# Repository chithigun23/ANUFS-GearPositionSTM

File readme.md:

# GearSensor STM32

Gear position sensor board for a MoTeC M150 paddle-shift system: an `STM32F072` reads a linear position sensor and the neutral switch, works out the current gear, and reports it to the ECU as an analog voltage, with a CAN transceiver on the ECU bus and status LEDs on the board. Powered from the M150 sensor 5 V or USB-C, and replaces the Arduino UNO R4 WiFi and shield build described on the [GearSensor project page](https://chithigunatilake.com/GearSensor/).

## Architecture

- **Power** - 5 V in from the M150 sensor supply (`SEN_5V`, J3) or from USB-C VBUS (`J1`). A `TPS2116` power mux (`U2`) gives the car priority and falls back to USB when the car rail drops below about 4 V (set by `R3`/`R4`, 300 k / 100 k). It blocks reverse current, so the ECU supply is never back-fed from a laptop and the laptop is never back-fed from the car. The mux status pin goes to `PA2` (`MUX_STAT`: high = car, low = USB). 1 uF on each mux input, a 300 mA polyfuse (`F1`) on the mux output and an `AP2112K-3.3` LDO (`U1`) after it. There is no reverse-polarity stage because a sensor supply cannot be reversed by the battery.
- **Compute** - `STM32F072CB` (`U6`, LQFP-48) with a 24 MHz `ABM8AIG` crystal on HSE, which CAN needs for accurate bit timing. Ferrite-filtered VDDA (`FB1`, with `C18` 1 uF and `C19` 10 nF after it), NRST and BOOT0 buttons.
- **Position and neutral sensing** - linear position sensor on J3 pin 7, scaled by `R5`/`R6` (10 k / 15 k) so a 5 V sensor swing lands inside the 3.3 V ADC range on `PA0`, with a 100 nF filter (`C20`) at the pin. Neutral switch on J3 pin 6 into `PB2` through `R28` (1 k). An `AQ1005-01ETG` TVS (`D1`, `D2`) on each harness input.
- **Gear output** - the STM32's own 12-bit DAC on `PA4` (output buffer off, so it can reach 0 V) drives a `TLV9062` op-amp (`U4`) at a gain of 1.5 (`R11` 4.99 k / `R12` 10 k) from the 5 V rail, giving the gear-position voltage on J3 pin 3 up to about 4.1 V through two 390 ohm 0603 series resistors (`R29`/`R30`) and a TVS (`D3`). `R10` (1 M) holds the output at 0 V until the firmware enables the DAC. A 10 k / 15 k divider (`R14`/`R15`, filtered by `C21`) reads the output back on `PA1` for closed-loop trim. The unused op-amp channel is tied off as a follower.
- **Status LEDs** - six `XL-2012SURUGC` red/green LEDs: `LED1` to `LED4` show the gear (or a fault) in combination, `LED5` shows MCU status and `LED6` shows the neutral switch. Their anodes share an `LED_5V` rail behind the slide switch `SW3`, which turns every LED off. Each die has its own series resistor (390 ohm red, 680 ohm green) and is sunk by a 5 V-tolerant MCU pin, so no driver is needed.
- **CAN** - `TCAN337` 3.3 V transceiver (`U5`) on `PB9` / `PB8`, with fault on `PB0` and silent mode on `PB1`. CAN+ / CAN- on J3 pins 5 and 4.
- **Debug and USB** - `J1` USB-C with 5.1 k CC pull-downs and a `USBLC6-2SC6` ESD array (`U3`) on D+ / D- into the MCU's native USB (`PA11` / `PA12`). 4-pin SWD header `J2` and a Tag-Connect TC2030 footprint `J4` (pads only, nothing to buy) on the same SWD, reset and 3.3 V nets. Test pads on the rails and every external signal.

The diagram is animated: dashes show the direction of flow, amber for power, teal for signals, blue for buses. If your viewer does not animate SVGs, the arrows still show the same paths.

## Car connector (J3)

Solder-wire pigtails, not a board connector: eight PTH pads in a row along the bottom edge (`gear:SolderWire-0.5sqmm_1x08_P4.2mm_D0.9mm_OD2.1mm_Relief_Anchored`, 1.15 mm holes for 0.5 mm² or smaller wire, 4.2 mm pitch), pin 1 on the right, labelled on both sides.

The pads are built not to tear out:

- **Annular ring:** 3.0 mm pads on 1.15 mm holes (0.93 mm ring), on all four copper layers, so the inner layers also hold the barrel.
- **Anchor vias:** two plated 0.3 mm vias inside each pad, on the side away from the relief hole (opposite the pull), through every layer. They rivet the pad copper to the board, and the GND pin's vias will also tie into the ground planes when they are poured.
- **Strain relief:** a 2.3 mm hole 3.6 mm from each pad towards the board edge, for insulation up to about 2.1 mm. The hole is plated (no net) so the wire bears on a smooth copper barrel instead of cut glass fibre, which chafes insulation under vibration. A silk ring marks each one, and "STRAIN RELIEF HOLES - DO NOT SOLDER" is printed directly under the row on both sides.

Fitting a wire: bring it in from the edge on the underside, up through its relief hole, across the top, and down into its pad, then solder it on the underside. Do not solder the relief hole. A pull on the harness then loads the relief hole, not the solder joint.

- **Vibration:** use abrasion-resistant insulation (ETFE/Tefzel, as most car harnesses do) and stake each wire to the board with RTV or a flexible adhesive at the relief hole and the pad. That stops the wire moving, which is what chafes the insulation and fatigues the wire where the solder stops wicking.
- **Edge web:** the board is 2 mm taller than square (50 x 52 mm) so there is 2.8 mm of FR4 between each relief hole and the bottom edge, which takes the pull. Still clamp the harness at the enclosure gland, so its weight does not hang off the board.

There are no cable-tie slots: the only free board edge beside the pigtail row is taken by the M3 mounting holes and their standoffs, so tie the harness to the enclosure at the cable gland instead.

| Pin | Net | Function |
|---|---|---|
| 1 | `SEN_5V` | M150 sensor 5 V in |
| 2 | `GND` | Ground |
| 3 | `GEAR_OUT` | Gear voltage out to the ECU |
| 4 | `CAN-` | CAN low |
| 5 | `CAN+` | CAN high |
| 6 | `NEUT_SW` | Neutral switch |
| 7 | `SPS` | Linear position sensor signal |
| 8 | - | Not connected |

## Status LEDs

Six red/green LEDs along the top edge, labelled on the silkscreen. Left to right: `NEUT` (`LED6`), `STAT` (`LED5`), `MODE` (`LED4`), then the code LEDs `4`, `2` and `1` (`LED3`, `LED2`, `LED1`). The three code LEDs read as a binary number. The same legend is on the back silkscreen. `SW3` (`LED ON/OFF`) turns every LED off in hardware.

| What you see | Meaning |
|---|---|
| `4 2 1` green, `MODE` green | Gear 1 to 6 in binary (1 = 001, 6 = 110). `111` is neutral. |
| `4 2 1` green, `MODE` amber | Shifting: the new gear, waiting for the actuator to return |
| `4 2 1` red, `MODE` red blinking 2 Hz | Unknown gear, reason code 1 to 3. Gear output 0 V. |
| `4 2 1` red, `MODE` red solid | Fault, reason code 4 to 7. Gear output 0 V. |
| `STAT` blinking 1 Hz | Firmware running: green on car power, amber on USB power, red while a fault is active. A steady or dark `STAT` means the main loop has stopped. |
| `NEUT` green | Neutral switch closed |
| `NEUT` red | Gear count and neutral switch disagree (reason 2) |

Reason codes: 1 not known at start-up, 2 position sensor count and neutral switch disagree, 3 neutral switch opened with no shift, 4 position sensor out of range, 5 position sensor did not return to rest, 6 gear output readback mismatch, 7 VDDA implausible. See the [firmware plan](docs/firmware-plan.md) for the state machine.

## Net classes

Set in the [project file](gearPosSens.kicad_pro), with three extra checks in [`gearPosSens.kicad_dru`](gearPosSens.kicad_dru). Stackup is JLCPCB's 4-layer default: 1 oz outer, 0.5 oz inner, 0.21 mm prepreg to In1. Every value is well above JLCPCB's 4-layer minimums (0.09 mm track and space, 0.13 mm via ring).

| Class | Nets | Track | Clearance | Via (pad / drill) | Why |
|---|---|---|---|---|---|
| `Power` | `SEN_5V`, `V_USB`, `MUX_OUT`, `+5V`, `+3V3`, `LED_5V` | 0.4 mm | 0.2 mm | 0.8 / 0.4 mm | About 1.2 A at a 10 C rise on 1 oz outer copper, 4 times the 300 mA fuse. The board draws under 0.2 A. |
| `GND` | `GND` | 0.4 mm | 0.2 mm | 0.6 / 0.3 mm | Mostly pours; small vias for stitching. |
| `USB` | `/inD+`, `/inD-`, `D+`, `D-` | 0.25 mm, 0.15 mm gap | 0.15 mm | 0.6 / 0.3 mm | About 90 ohm differential on the outer layer (IPC-2141 estimate). USB full speed is not critical over this length, but the pair should stay coupled. |
| `CAN` | `CAN+`, `CAN-` | 0.3 mm, 0.3 mm gap | 0.3 mm | 0.6 / 0.3 mm | Harness signals, routed as a pair. |
| `Harness` | `SPS`, `NEUT_SW`, `GEAR_OUT` | 0.3 mm | 0.3 mm | 0.6 / 0.3 mm | Come in from the car and take transients before the TVS clamps them. |
| `Analog` | `VDDA`, `SPS_DIV`, `GEAR_OUT_DIV`, `GEAR_OUT_3V3`, op-amp and mux-threshold nodes | 0.25 mm | 0.2 mm | 0.6 / 0.3 mm | Low current; keep short and away from the LED and CAN lines. |
| `Default` | Everything else (LED drives, SWD, crystal, CAN logic, reset, boot) | 0.2 mm | 0.2 mm | 0.6 / 0.3 mm | Logic signals, a few mA each. |

The custom rules:

- Power and GND tracks may neck down to 0.3 mm on the outer layers to enter the 0.3 mm pins of `U2` and `U6`.
- Power and GND tracks on the inner layers must be 0.8 mm or wider, because 0.5 oz copper carries about a third of the current. Keep power on the outer layers or in pours where you can.
- USB tracks keep 0.3 mm from any other net's tracks, vias and pours.

Use two vias wherever a power track changes layer. The `Analog` class names three nets by their auto-generated names (`Net-(R11-Pad2)`, `Net-(U4A--)`, `Net-(U2-PR1)`). If the schematic is re-annotated, re-check that those nets are still in `Analog`.

## From the Arduino version

- Same job, same sensors, same ECU interface. The shift logic, trust model and FMEA are documented on the [project page](https://chithigunatilake.com/GearSensor/).
- One board replaces the Arduino UNO R4 WiFi and shield.
- The gear-voltage output is read back through an ADC pin again, which version 2 of the Arduino build dropped.
- Status LEDs replace the LED matrix. This board has no WiFi or Bluetooth, so the phone display does not carry over. USB-C and the SWD header are the way in for programming and debug.
- The firmware is in Rust ([`firmware/`](firmware)), written to the [firmware plan](docs/firmware-plan.md). It builds and its logic is unit tested on the PC, but it has not run on a board yet.

## Status

Work in progress. The 50 x 52 mm PCB is placed but not yet routed. The firmware builds and its logic tests pass on the PC; it has not been flashed to a board. Not run on a car.

## Repo contents

- [KiCad project](gearPosSens.kicad_pro)
- [Schematic](gearPosSens.kicad_sch)
- [PCB layout](gearPosSens.kicad_pcb)
- [Power and gear-output design notes](power-mux-notes.md)
- [Firmware](firmware) (Rust, Embassy)
- [Firmware plan](docs/firmware-plan.md) and its [architecture diagram](docs/firmware-architecture.svg)
- [Symbols, footprints and 3D models](library)

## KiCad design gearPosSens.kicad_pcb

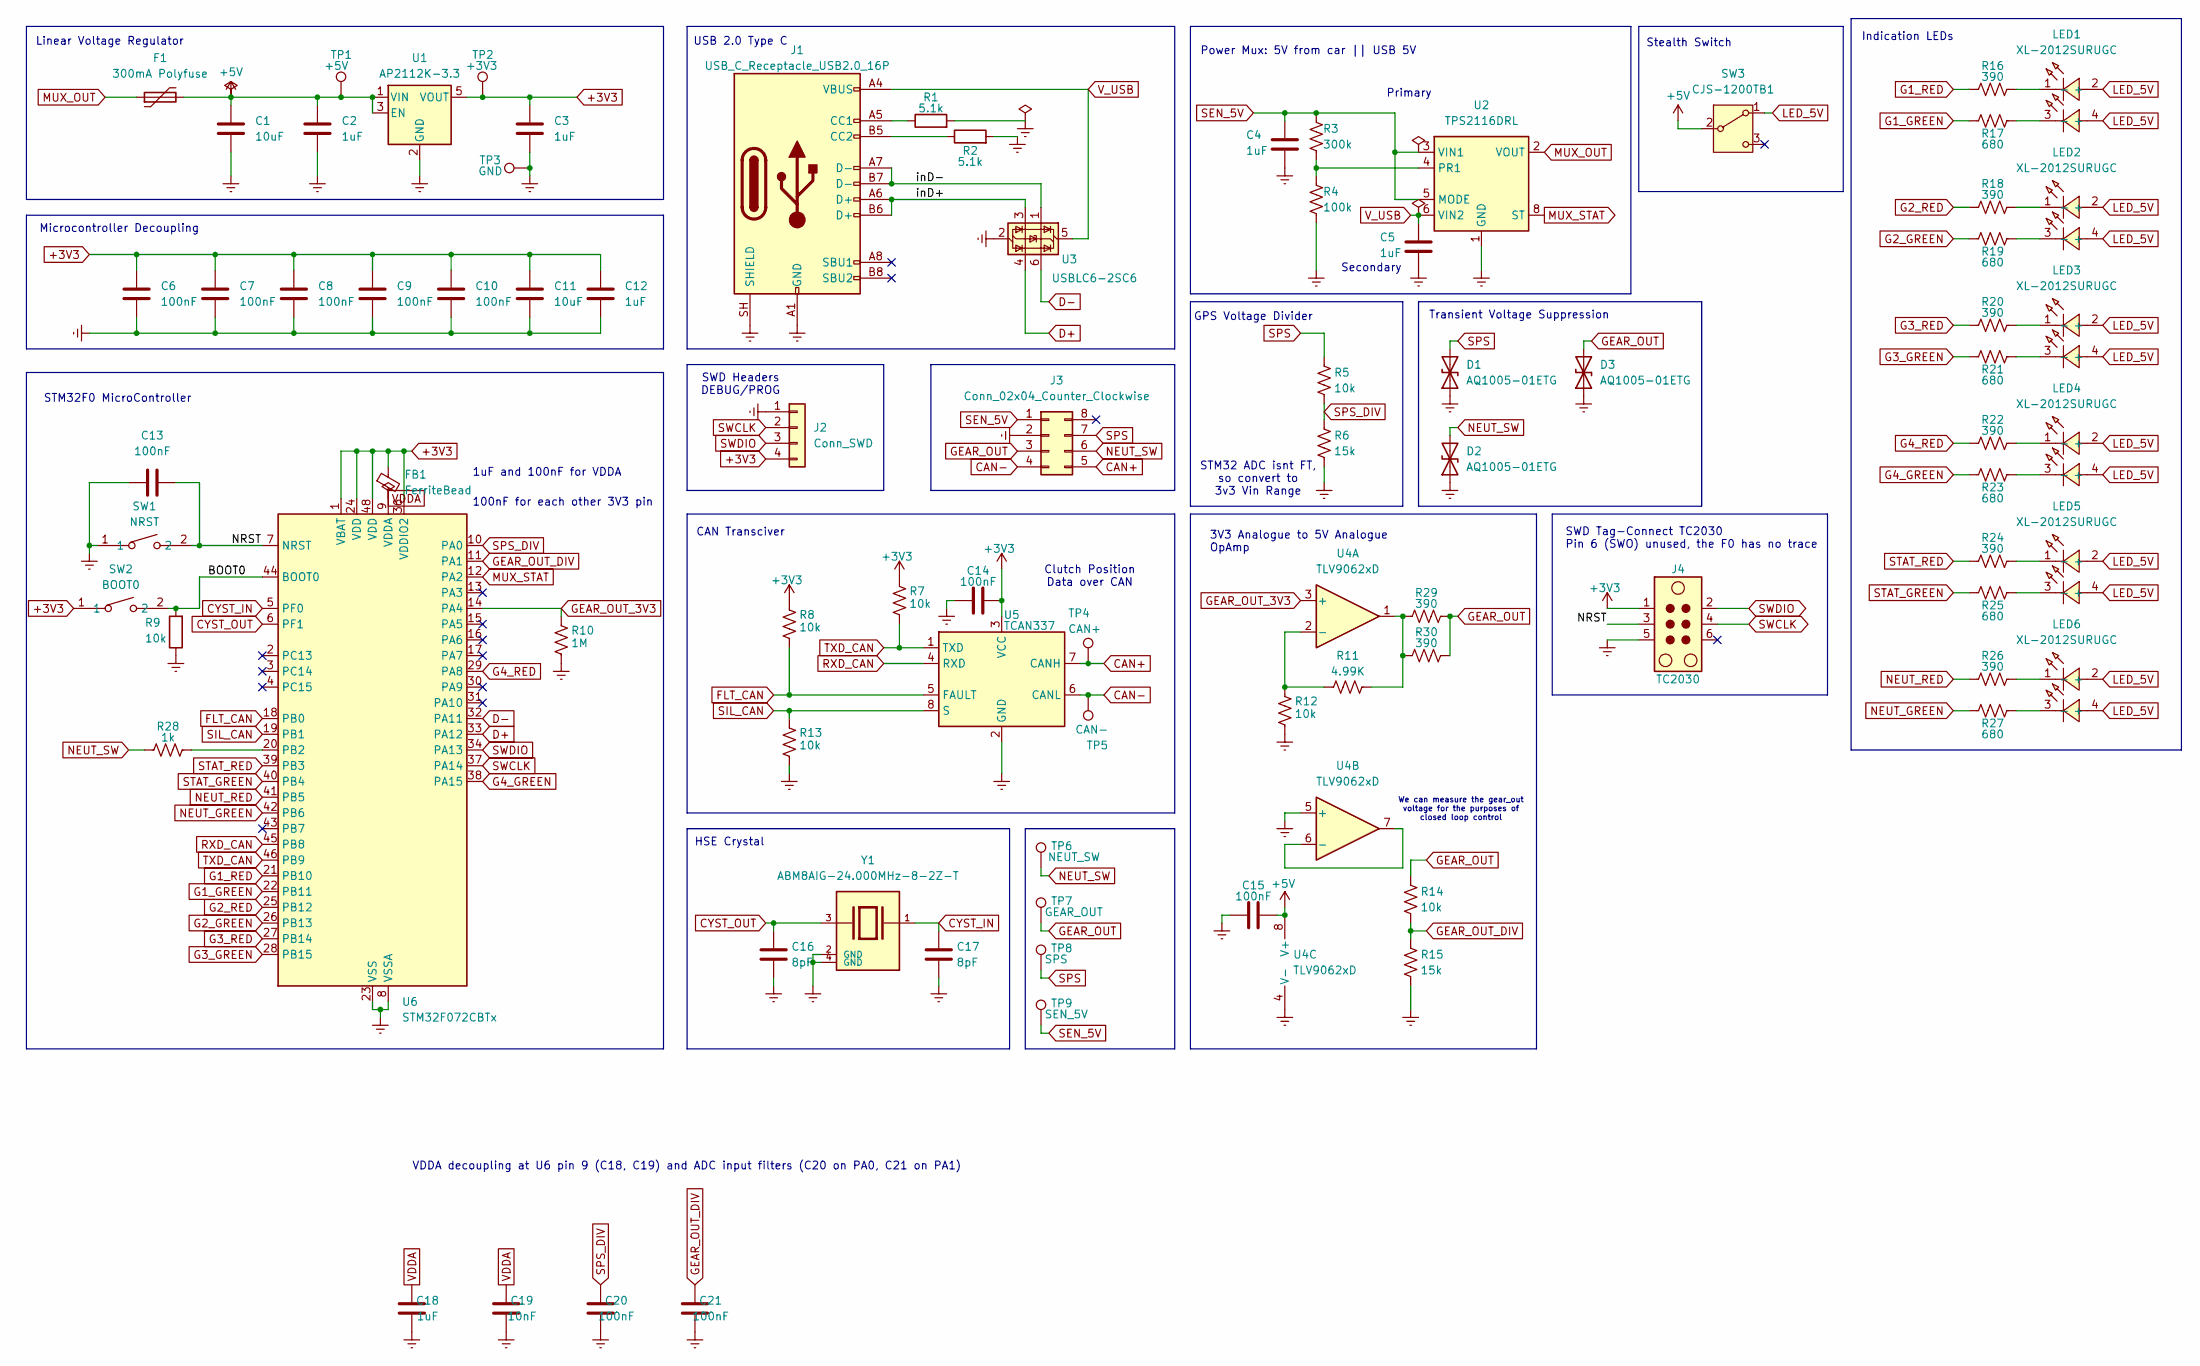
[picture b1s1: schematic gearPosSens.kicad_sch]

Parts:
C1, C11: 10uF; C_0805_2012Metric_Pad1.18x1.45mm_HandSolder
C2, C3, C4, C5, C12: 1uF; C_0805_2012Metric_Pad1.18x1.45mm_HandSolder
C6, C7, C8, C9, C10, C13, C14, C15: 100nF; C_0805_2012Metric_Pad1.18x1.45mm_HandSolder
C16, C17: 8pF; C_0402_1005Metric_Pad0.74x0.62mm_HandSolder
C18: 1uF; C_0402_1005Metric_Pad0.74x0.62mm_HandSolder
C19: 10nF; C_0402_1005Metric_Pad0.74x0.62mm_HandSolder
C20, C21: 100nF; C_0402_1005Metric_Pad0.74x0.62mm_HandSolder
D1, D2, D3: AQ1005-01ETG; MPN AQ1005-01ETG
F1: 300mA Polyfuse; Fuse_0805_2012Metric_Pad1.15x1.40mm_HandSolder
FB1: FerriteBead; L_0402_1005Metric_Pad0.77x0.64mm_HandSolder
J1: USB_C_Receptacle_USB2.0_16P; USB-C-SMD_TYPE-C-16PIN-2MD-073; MPN TYPE-C 16PIN 2MD(073); LCSC Part C2765186
J2: Conn_SWD; PinHeader_1x04_P2.54mm_Vertical
J3: Conn_02x04_Counter_Clockwise; SolderWire-0.5sqmm_1x08_P4.2mm_D0.9mm_OD2.1mm_Relief_Anchor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
J4: TC2030; Tag-Connect_TC2030-IDC-FP_2x03_P1.27mm_Vertical
LED1, LED2, LED3, LED4, LED5, LED6: XL-2012SURUGC; MPN XL-2012SURUGC; LCSC Part C965845
R1, R2: 5.1k; R_0805_2012Metric_Pad1.20x1.40mm_HandSolder
R3: 300k; R_0805_2012Metric_Pad1.20x1.40mm_HandSolder
R4: 100k; R_0805_2012Metric_Pad1.20x1.40mm_HandSolder
R5, R7, R8, R9, R12, R13, R14: 10k; R_0805_2012Metric_Pad1.20x1.40mm_HandSolder
R6, R15: 15k; R_0805_2012Metric_Pad1.20x1.40mm_HandSolder
R10: 1M; R_0805_2012Metric_Pad1.20x1.40mm_HandSolder
R11: 4.99K; R_0402_1005Metric_Pad0.72x0.64mm_HandSolder
R16, R18, R20, R22, R24, R26: 390; R_0402_1005Metric_Pad0.72x0.64mm_HandSolder
R17, R19, R21, R23, R25, R27: 680; R_0402_1005Metric_Pad0.72x0.64mm_HandSolder
R28: 1k; R_0402_1005Metric_Pad0.72x0.64mm_HandSolder
R29, R30: 390; R_0603_1608Metric_Pad0.98x0.95mm_HandSolder
SW1: NRST; SW-SMD_L3.9-W3.0-P4.45; MPN TS-1088-AR02016; LCSC Part C720477
SW2: BOOT0; SW-SMD_L3.9-W3.0-P4.45; MPN TS-1088-AR02016; LCSC Part C720477
SW3: CJS-1200TB1; MPN CJS-1200TB1; LCSC Part C2921631
TP1: +5V; TestPoint_THTPad_D2.0mm_Drill1.0mm
TP2: +3V3; TestPoint_THTPad_D2.0mm_Drill1.0mm
TP3: GND; TestPoint_THTPad_D2.0mm_Drill1.0mm
TP4: CAN+; TestPoint_THTPad_D2.0mm_Drill1.0mm
TP5: CAN-; TestPoint_THTPad_D2.0mm_Drill1.0mm
TP6: NEUT_SW; TestPoint_THTPad_D2.0mm_Drill1.0mm
TP7: GEAR_OUT; TestPoint_THTPad_D2.0mm_Drill1.0mm
TP8: SPS; TestPoint_THTPad_D2.0mm_Drill1.0mm
TP9: SEN_5V; TestPoint_THTPad_D2.0mm_Drill1.0mm
U1: AP2112K-3.3; SOT-23-5_HandSoldering
U2: TPS2116DRL; SOT-583-8
U3: USBLC6-2SC6; SOT-23-6
U4: TLV9062xD; SOIC-8_3.9x4.9mm_P1.27mm
U5: TCAN337; SOIC-8_3.9x4.9mm_P1.27mm
U6: STM32F072CBTx; LQFP-48_7x7mm_P0.5mm
Y1: ABM8AIG-24.000MHz-8-2Z-T; ABM8AIG-24.000MHZ-8-2Z-T; PARTREV 43629

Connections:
+3V3: C3.1, C6.2, C7.2, C8.2, C9.2, C10.2, C11.2, C12.1, C14.2, FB1.1, J2.4, J4.1, R7.1, R8.1, SW2.1, TP2.1, U1.5 (VOUT), U5.3 (VCC), U6.1 (VBAT), U6.24 (VDD), U6.36 (VDDIO2), U6.48 (VDD)
+5V: C1.2, C2.1, C15.2, F1.2, SW3.2 (B), TP1.1, U1.1 (VIN), U1.3 (EN), U4.8 (V+)
/BOOT0: R9.2, SW2.2, U6.44 (BOOT0)
/NRST: C13.2, J4.3, SW1.2, U6.7 (NRST)
/inD+: J1.A6 (D+), J1.B6 (D+), U3.3 (I/O2)
/inD-: J1.A7 (D-), J1.B7 (D-), U3.1 (I/O1)
CAN+: J3.5, TP4.1, U5.7 (CANH)
CAN-: J3.4, TP5.1, U5.6 (CANL)
CYST_IN: C17.1, U6.5 (PF0), Y1.1
CYST_OUT: C16.1, U6.6 (PF1), Y1.3
D+: U3.4 (I/O2), U6.33 (PA12)
D-: U3.6 (I/O1), U6.32 (PA11)
FLT_CAN: R8.2, U5.5 (FAULT), U6.18 (PB0)
G1_GREEN: R17.2, U6.22 (PB11)
G1_RED: R16.1, U6.21 (PB10)
G2_GREEN: R19.2, U6.26 (PB13)
G2_RED: R18.1, U6.25 (PB12)
G3_GREEN: R21.2, U6.28 (PB15)
G3_RED: R20.1, U6.27 (PB14)
G4_GREEN: R23.2, U6.38 (PA15)
G4_RED: R22.1, U6.29 (PA8)
GEAR_OUT: D3.2 (A2), J3.3, R14.1, R29.2, R30.2, TP7.1
GEAR_OUT_3V3: R10.1, U4.3 (+), U6.14 (PA4)
GEAR_OUT_DIV: C21.1, R14.2, R15.1, U6.11 (PA1)
GND: C1.1, C2.2, C3.2, C4.1, C5.1, C6.1, C7.1, C8.1, C9.1, C10.1, C11.1, C12.2, C13.1, C14.1, C15.1, C16.2, C17.2, C18.2, C19.2, C20.2, C21.2, D1.1 (A1), D2.1 (A1), D3.1 (A1), J1.A1 (GND), J1.A12 (GND), J1.B1 (GND), J1.B12 (GND), J1.SH (SHIELD), J2.1, J3.2, J4.5, R1.2, R2.2, R4.2, R6.2, R9.1, R10.2, R12.2, R13.2, R15.2, SW1.1, TP3.1, U1.2 (GND), U2.1 (GND), U3.2 (GND), U4.4 (V-), U4.5 (+), U5.2 (GND), U6.8 (VSSA), U6.23 (VSS), U6.35 (VSS), U6.47 (VSS), Y1.2 (GND), Y1.4 (GND)
LED_5V: LED1.2 (+), LED1.4 (+), LED2.2 (+), LED2.4 (+), LED3.2 (+), LED3.4 (+), LED4.2 (+), LED4.4 (+), LED5.2 (+), LED5.4 (+), LED6.2 (+), LED6.4 (+), SW3.1 (A)
MUX_OUT: F1.1, U2.2 (VOUT), U2.7 (VOUT)
MUX_STAT: U2.8 (ST), U6.12 (PA2)
NEUT_GREEN: R27.2, U6.42 (PB6)
NEUT_RED: R26.1, U6.41 (PB5)
NEUT_SW: D2.2 (A2), J3.6, R28.1, TP6.1
unnamed: J1.A5 (CC1), R1.1
unnamed: J1.B5 (CC2), R2.1
unnamed: LED1.1 (-), R16.2
unnamed: LED1.3 (-), R17.1
unnamed: LED2.1 (-), R18.2
unnamed: LED2.3 (-), R19.1
unnamed: LED3.1 (-), R20.2
unnamed: LED3.3 (-), R21.1
unnamed: LED4.1 (-), R22.2
unnamed: LED4.3 (-), R23.1
unnamed: LED5.1 (-), R24.2
unnamed: LED5.3 (-), R25.1
unnamed: LED6.1 (-), R26.2
unnamed: LED6.3 (-), R27.1
unnamed: R11.2, R29.1, R30.1, U4.1
unnamed: R3.2, R4.1, U2.4 (PR1)
unnamed: R11.1, R12.1, U4.2 (-)
unnamed: U4.6 (-), U4.7
unnamed: R28.2, U6.20 (PB2)
RXD_CAN: U5.4 (RXD), U6.45 (PB8)
SEN_5V: C4.2, J3.1, R3.1, TP9.1, U2.3 (VIN1), U2.5 (MODE)
SIL_CAN: R13.1, U5.8 (S), U6.19 (PB1)
SPS: D1.2 (A2), J3.7, R5.1, TP8.1
SPS_DIV: C20.1, R5.2, R6.1, U6.10 (PA0)
STAT_GREEN: R25.2, U6.40 (PB4)
STAT_RED: R24.1, U6.39 (PB3)
SWCLK: J2.2, J4.4, U6.37 (PA14)
SWDIO: J2.3, J4.2, U6.34 (PA13)
TXD_CAN: R7.2, U5.1 (TXD), U6.46 (PB9)
VDDA: C18.1, C19.1, FB1.2, U6.9 (VDDA)
V_USB: C5.2, J1.A4 (VBUS), J1.A9 (VBUS), J1.B4 (VBUS), J1.B9 (VBUS), U2.6 (VIN2), U3.5 (VBUS)

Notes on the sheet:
We can measure the gear_out voltage for the purposes of closed loop control
Indication LEDs
Transient Voltage Suppression
GPS Voltage Divider
100nF for each other 3V3 pin
Microcontroller Decoupling
3V3 Analogue to 5V Analogue OpAmp
CAN Transciver
SWD Tag-Connect TC2030 Pin 6 (SWO) unused, the F0 has no trace
Secondary
Stealth Switch
SWD Headers DEBUG/PROG
Power Mux: 5V from car || USB 5V
HSE Crystal
1uF and 100nF for VDDA
Clutch Position Data over CAN
USB 2.0 Type C
Linear Voltage Regulator
Primary
STM32F0 MicroController
STM32 ADC isnt FT, so convert to 3v3 Vin Range
VDDA decoupling at U6 pin 9 (C18, C19) and ADC input filters (C20 on PA0, C21 on PA1)

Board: 4 copper layers, 89 parts (0 on the bottom side), 62 nets, no tracks yet.

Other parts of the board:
H1, H2, H3, H4: M3; MountingHole_3.2mm_M3_Pad

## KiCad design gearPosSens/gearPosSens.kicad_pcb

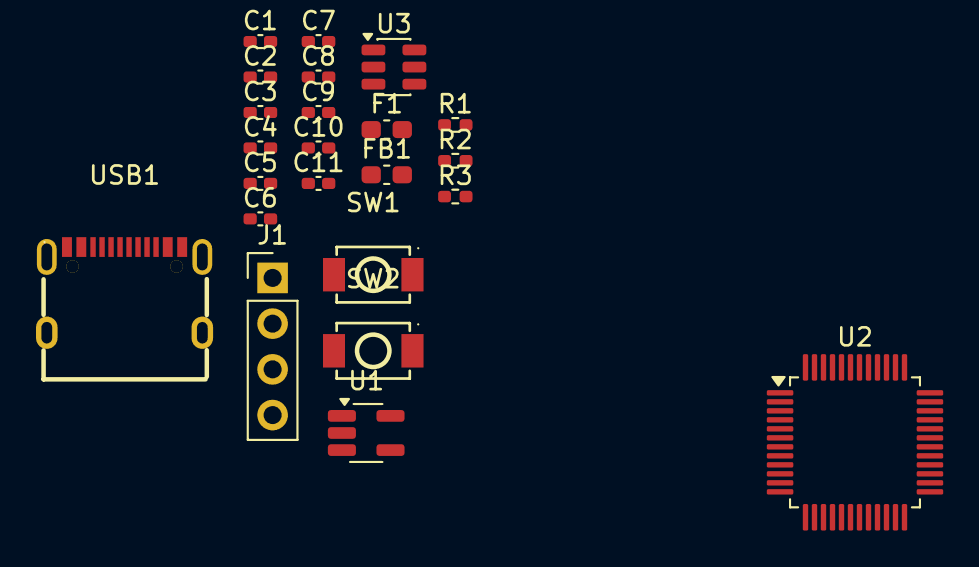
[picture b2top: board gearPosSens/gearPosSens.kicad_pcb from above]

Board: 4 copper layers, 23 parts (0 on the bottom side), 15 nets, no tracks yet.

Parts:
C1, C9: 10uF; C_0402_1005Metric_Pad0.74x0.62mm_HandSolder
C2, C3, C11: 1uF; C_0402_1005Metric_Pad0.74x0.62mm_HandSolder
C4, C5, C6, C7, C8, C10: 100nF; C_0402_1005Metric_Pad0.74x0.62mm_HandSolder
F1: 100mA Polyfuse; C_0603_1608Metric_Pad1.08x0.95mm_HandSolder
FB1: FerriteBead; C_0603_1608Metric_Pad1.08x0.95mm_HandSolder
J1: Conn_SWD; PinHeader_1x04_P2.54mm_Vertical
R1: 10k; R_0402_1005Metric_Pad0.72x0.64mm_HandSolder
R2, R3: 5.1k; R_0402_1005Metric_Pad0.72x0.64mm_HandSolder
SW1: NRST; SW-SMD_L3.9-W3.0-P4.45
SW2: BOOT0; SW-SMD_L3.9-W3.0-P4.45
U1: AP2112K-3.3; SOT-23-5_HandSoldering
U2: STM32F072CBTx; LQFP-48_7x7mm_P0.5mm
U3: USBLC6-2SC6; SOT-23-6
USB1: TYPE-C 16PIN 2MD; USB-C-SMD_TYPE-C-16PIN-2MD-073

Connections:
+3V3: C3.1, C4.2, C5.2, C6.2, C7.2, C8.2, C9.2, C11.1, FB1.1, J1.4, SW2.1, U1.5 (VOUT), U2.1 (VBAT), U2.24 (VDD), U2.36 (VDDIO2), U2.48 (VDD)
/BOOT0: R1.2, SW2.2, U2.44 (BOOT0)
/NRST: C10.2, SW1.2, U2.7 (NRST)
/VIN_LDO: C1.2, C2.1, F1.2, U1.1 (VIN), U1.3 (EN)
/inD+: U3.3 (I/O2), USB1.A6 (Dp1), USB1.B6 (Dp2)
/inD-: U3.1 (I/O1), USB1.A7 (Dn1), USB1.B7 (Dn2)
D+: U2.33 (PA12), U3.4 (I/O2)
D-: U2.32 (PA11), U3.6 (I/O1)
GND: C1.1, C2.2, C3.2, C4.1, C5.1, C6.1, C7.1, C8.1, C9.1, C10.1, C11.2, J1.1, R1.1, R2.2, R3.2, SW1.1, U1.2 (GND), U2.8 (VSSA), U2.23 (VSS), U2.35 (VSS), U2.47 (VSS), U3.2 (GND), USB1.13 (EH), USB1.14 (EH), USB1.A1B12 (GND), USB1.B1A12 (GND)
unnamed: FB1.2, U2.9 (VDDA)
unnamed: R2.1, USB1.A5 (CC1)
unnamed: R3.1, USB1.B5 (CC2)
SWCLK: J1.2, U2.37 (PA14)
SWDIO: J1.3, U2.34 (PA13)
VBUS: F1.1, U3.5 (VBUS), USB1.A4B9 (VBUS), USB1.B4A9 (VBUS)

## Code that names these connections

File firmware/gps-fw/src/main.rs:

//! Gear position sensor firmware: STM32F072CB, one 5 ms loop (docs/firmware-plan.md).
//!
//! Every tick: scan the LPS, the gear output readback and VREFINT four times each, run the
//! logic in `gps-core`, write the DAC, update the LEDs every second tick, feed the watchdog.
//! All decisions live in `gps-core`; this file only touches hardware.

#![no_std]
#![no_main]

use defmt::{info, warn};
use embassy_executor::Spawner;
use embassy_stm32::adc::{self, Adc, SampleTime};
use embassy_stm32::dac::{DacChannel, Value};
use embassy_stm32::gpio::{AnyPin, Input, Level, Output, OutputOpenDrain, Pull, Speed};
use embassy_stm32::time::Hertz;
use embassy_stm32::wdg::IndependentWatchdog;
use embassy_stm32::{Peri, bind_interrupts, pac, peripherals};
use embassy_time::{Duration, Instant, Ticker, Timer};
use gps_core::config::NOMINAL;
use gps_core::led::LedFrame;
use gps_core::{Core, Sample};
use {defmt_rtt as _, panic_probe as _};

/// `PB2` internal pull-up for the neutral switch. Measure the car's neutral wire with the switch
/// open first: if it sits above 3.6 V (a neutral lamp), set this to false.
const NEUTRAL_PULLUP: bool = true;

/// Watchdog timeout. The LSI runs 30 to 60 kHz, so 75 ms nominal is 50 to 100 ms real.
const WATCHDOG_US: u32 = 75_000;

/// ADC sample time: 71.5 cycles, fine for the 6 kohm dividers and VREFINT.
const SAMPLE: SampleTime = SampleTime::CYCLES71_5;

/// Factory VREFINT calibration word, taken at 3.3 V (STM32F072 datasheet).
const VREFINT_CAL_ADDR: usize = 0x1FFF_F7BA;

bind_interrupts!(struct Irqs {
    ADC1_COMP => adc::InterruptHandler<peripherals::ADC1>;
});

fn clocks() -> embassy_stm32::Config {
    use embassy_stm32::rcc::*;
    let mut c = embassy_stm32::Config::default();
    // 24 MHz crystal on HSE (CAN-grade accuracy), PLL x2 to 48 MHz.
    c.rcc.hse = Some(Hse {
        freq: Hertz(24_000_000),
        mode: HseMode::Oscillator,
    });
    c.rcc.pll = Some(Pll {
        src: PllSource::HSE,
        prediv: PllPreDiv::DIV1,
        mul: PllMul::MUL2,
    });
    c.rcc.sys = Sysclk::PLL1_P;
    c
}

fn vrefint_cal() -> u16 {
    // SAFETY: a read-only system-memory word that is always present on the STM32F072.
    #[allow(unsafe_code)]
    unsafe {
        core::ptr::read_volatile(VREFINT_CAL_ADDR as *const u16)
    }
}

/// Twelve open-drain LED cathodes: low lights a die. Index 0 is `LED1`.
struct Leds {
    red: [OutputOpenDrain<'static>; 6],
    green: [OutputOpenDrain<'static>; 6],
}

impl Leds {
    fn show(&mut self, f: &LedFrame) {
        for (pin, on) in self.red.iter_mut().zip(f.red) {
            pin.set_level(if on { Level::Low } else { Level::High });
        }
        for (pin, on) in self.green.iter_mut().zip(f.green) {
            pin.set_level(if on { Level::Low } else { Level::High });
        }
    }
}

#[embassy_executor::main]
async fn main(_spawner: Spawner) {
    let p = embassy_stm32::init(clocks());

    // CAN stays silent from the start: PB1 high puts the TCAN337 in silent mode, PB9 (TXD) is
    // left as an input so R7 holds the bus recessive, and the bxCAN clock stays off.
    let _can_silent = Output::new(p.PB1, Level::High, Speed::Low);

    // DAC: code 0 first, output buffer off (so it can reach 0 V), then enable.
    let mut dac = DacChannel::new_blocking(p.DAC1, p.PA4);
    dac.set(Value::Bit12Right(0));
    dac.disable();
    pac::DAC1.cr().modify(|w| w.set_boff(0, true));
    dac.enable();

    // Reset cause: a watchdog reset is a warning only; the output starts at 0 V regardless.
    let csr = pac::RCC.csr().read();
    if csr.iwdgrstf() {
        warn!("reset by the independent watchdog");
    }
    pac::RCC.csr().modify(|w| w.set_rmvf(true));

    let neutral = Input::new(p.PB2, if NEUTRAL_PULLUP { Pull::Up } else { Pull::None });
    let mux_stat = Input::new(p.PA2, Pull::Up); // TPS2116 ST: open-drain, high = car

    let od = |pin: Peri<'static, AnyPin>| OutputOpenDrain::new(pin, Level::High, Speed::Low);
    let mut leds = Leds {
        red: [
            od(p.PB10.into()),
            od(p.PB12.into()),
            od(p.PB14.into()),
            od(p.PA8.into()),
            od(p.PB3.into()),
            od(p.PB5.into()),
        ],
        green: [
            od(p.PB11.into()),
            od(p.PB13.into()),
            od(p.PB15.into()),
            od(p.PA15.into()),
            od(p.PB4.into()),
            od(p.PB6.into()),
        ],
    };

    // The F0 ADC runs from its own 14 MHz HSI14 clock (CKMODE reset value). The HAL assumes it is
    // running but does not start it, so start it before the ADC calibrates.
    pac::RCC.cr2().modify(|w| w.set_hsi14on(true));
    while !pac::RCC.cr2().read().hsi14rdy() {}

    let mut adc = Adc::new(p.ADC1, Irqs);
    let mut vref = adc.enable_vref();
    Timer::after_micros(10).await; // VREFINT start-up
    let mut lps = p.PA0;
    let mut readback = p.PA1;

    // Average VREFINT 64 times before any decision.
    let cal = vrefint_cal();
    let mut acc = 0u32;
    for _ in 0..64 {
        acc += u32::from(adc.read(&mut vref, SAMPLE).await);
    }
    let vdda = gps_core::cal::vdda_mv(acc / 64, u32::from(cal), &NOMINAL);
    info!("VREFINT_CAL {}, VDDA {} mV", cal, vdda);

    let mut wdg = IndependentWatchdog::new(p.IWDG, WATCHDOG_US);
    wdg.unleash();

    let mut core = Core::new(NOMINAL);
    let start = Instant::now();
    let mut ticker = Ticker::every(Duration::from_millis(u64::from(NOMINAL.tick_ms)));
    let mut led_tick = false;
    let mut last_state = core.state();
    info!("running, state {}", last_state);

    loop {
        // 1. Scan IN0, IN1 and IN17 four times and average.
        let (mut a, mut b, mut v) = (0u32, 0u32, 0u32);
        for _ in 0..4 {
            a += u32::from(adc.read(&mut lps, SAMPLE).await);
            b += u32::from(adc.read(&mut readback, SAMPLE).await);
            v += u32::from(adc.read(&mut vref, SAMPLE).await);
        }

        // 2. Digital inputs. 3. Logic.
        let o = core.tick(&Sample {
            lps_raw: (a / 4) as u16,
            readback_raw: (b / 4) as u16,
            vrefint_raw: (v / 4) as u16,
            vrefint_cal: cal,
            neutral_closed: neutral.is_low(),
            on_usb: mux_stat.is_low(),
            time_ms: start.elapsed().as_millis() as u32,
        });

        // 4. DAC.
        dac.set(Value::Bit12Right(o.dac_code));

        // 5. LEDs every second tick (10 ms).
        led_tick = !led_tick;
        if led_tick {
            leds.show(&o.leds);
        }

        if o.status.state != last_state {
            last_state = o.status.state;
            info!(
                "state {} target {} mV code {} lps {} mV readback {} mV vdda {} mV",
                o.status.state, o.status.target_mv, o.dac_code, o.lps_mv, o.readback_mv, o.vdda_mv
            );
        }
        if o.out.clamped || o.out.trim_at_limit {
            warn!("output warning {}", o.out);
        }

        // 6. Watchdog.
        wdg.pet();
        ticker.next().await;
    }
}
